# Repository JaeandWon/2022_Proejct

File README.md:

## 융합 프로젝트 10조
주제: PID 제어기를 이용한 밸런싱 로봇 제어

## 기술스택
- Control: PID, Complementary Filter 
- Protocol: mqtt, socket  
- Server: nodeJs  
- HW(MCU) : Arduino(esp32)
- PCB tool: KiCAD  

## Schematic 

## 3D Model

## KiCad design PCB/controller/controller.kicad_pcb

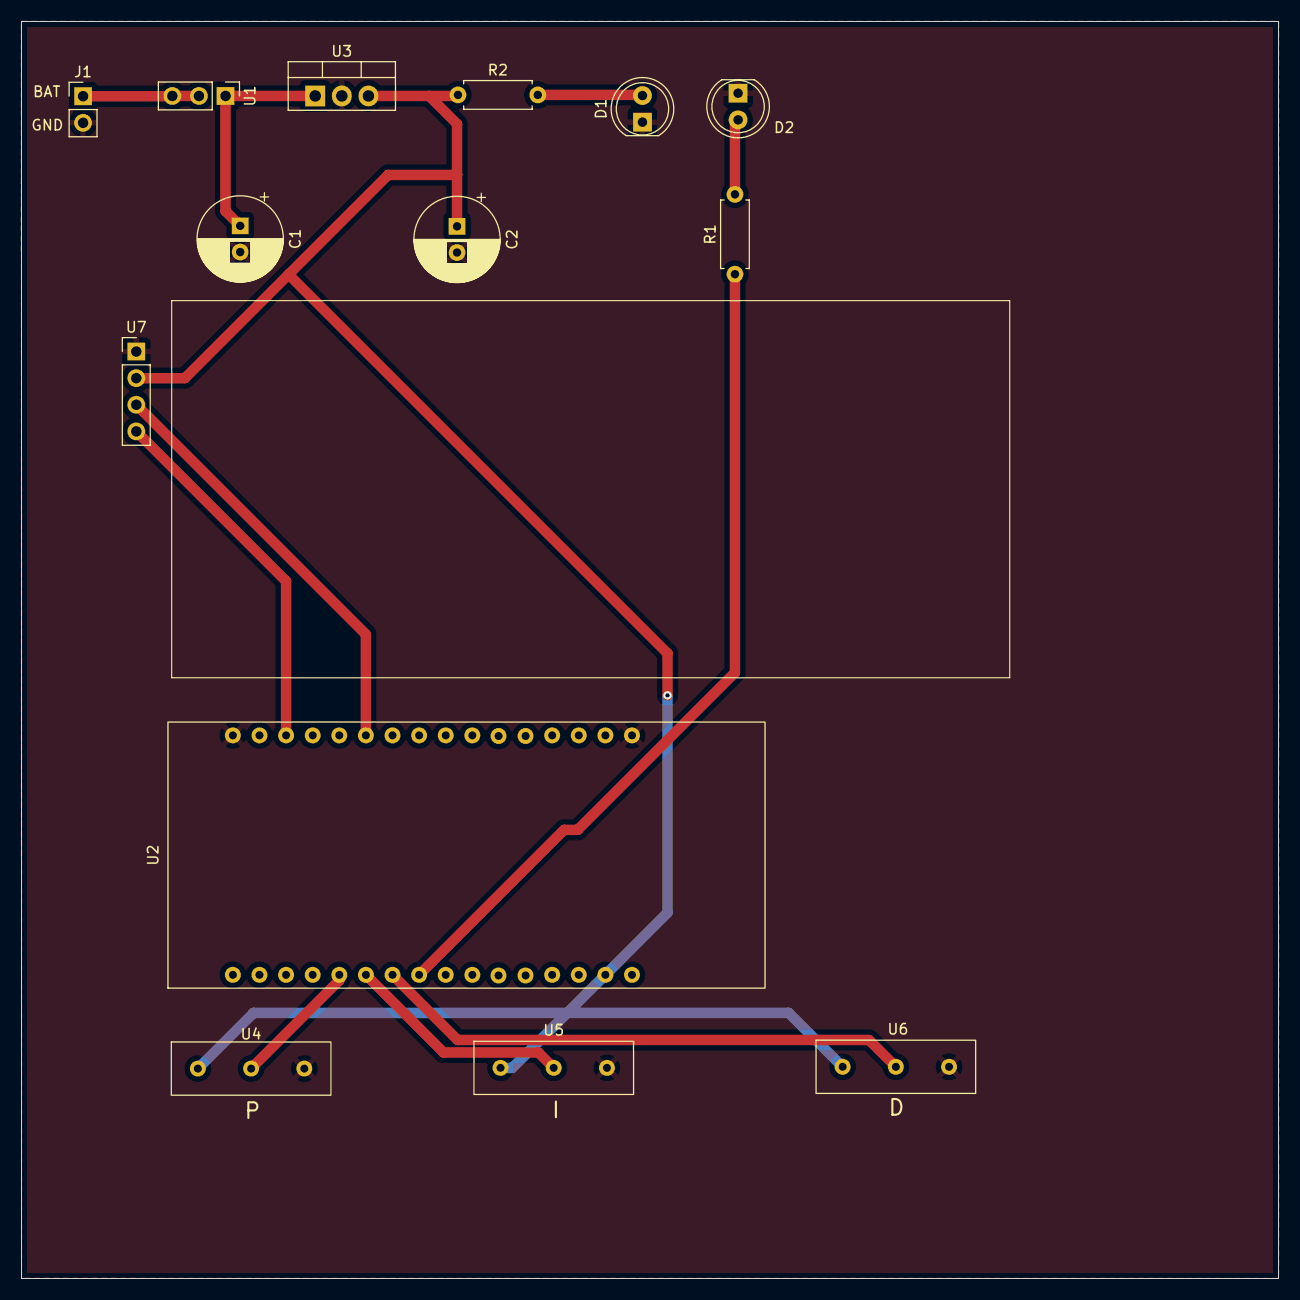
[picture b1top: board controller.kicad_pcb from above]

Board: 2 copper layers, 120.0 x 120.0 mm, 14 parts (0 on the bottom side), 12 nets.

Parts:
C1, C2: CAP; CP_Radial_D8.0mm_P2.50mm
D1, D2: LED; LED_D5.0mm
J1: Connector2; PinHeader_1x02_P2.54mm_Vertical
R1: 40; R_Axial_DIN0207_L6.3mm_D2.5mm_P7.62mm_Horizontal
R2: 330; R_Axial_DIN0207_L6.3mm_D2.5mm_P7.62mm_Horizontal
U1: Switch1; PinHeader_1x03_P2.54mm_Vertical
U2: Loline_d_32
U3: L7805; TO-220-3_Vertical
U4: Kp; variable_R
U5: Ki; variable_R
U6: Kd; variable_R
U7: LCD; PinHeader_1x04_P2.54mm_Vertical

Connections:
+5V: C2.1, R2.1, U2.USB, U3.3 (OUT), U4.1, U5.1, U6.1, U7.2
+BATT: C1.1, U1.1, U3.1 (IN)
+BATT_IN: J1.1, U1.2, U1.3
/Kd: U2.33, U6.2
/Ki: U2.32, U5.2
/Kp: U2.34, U4.2
/SCL: U2.22, U7.4
/SDA: U2.21, U7.3
/WF_LED2: R1.1, U2.25
GND: C1.2, C2.2, D1.1 (K), D2.1 (K), J1.2, U2.GND, U3.2 (GND), U4.3, U5.3, U6.3, U7.1
unnamed: D1.2 (A), R2.2
unnamed: D2.2 (A), R1.2

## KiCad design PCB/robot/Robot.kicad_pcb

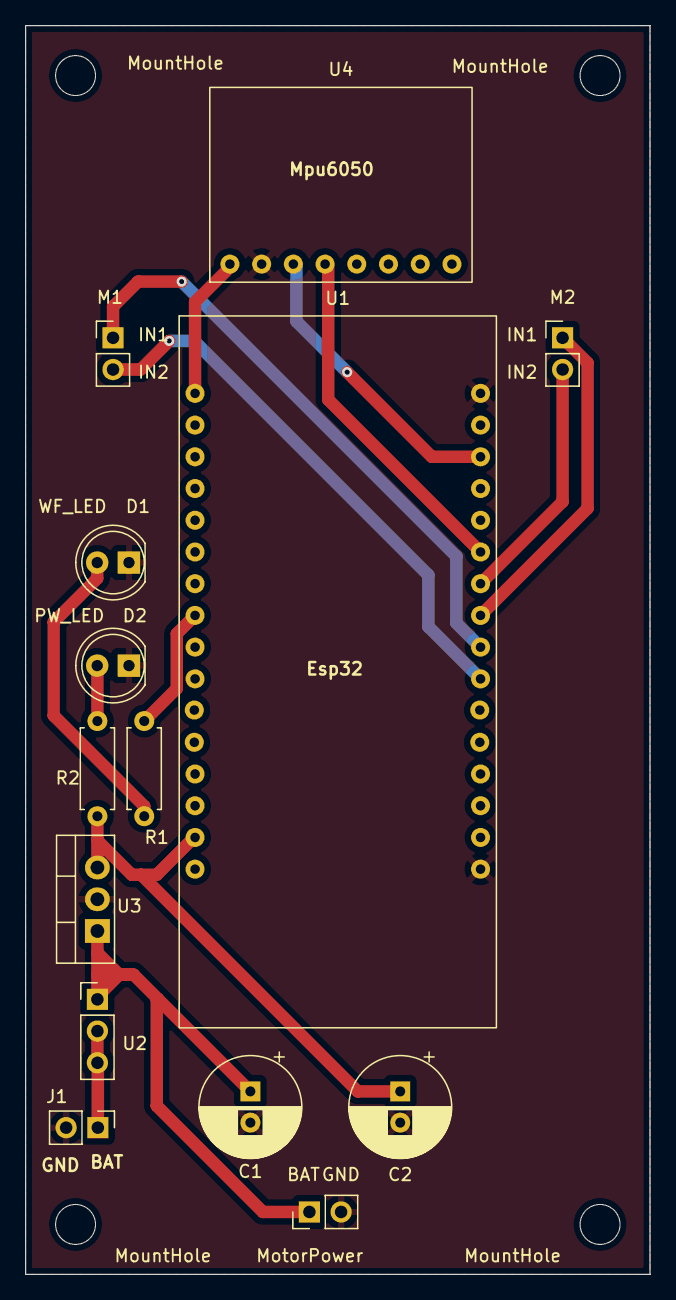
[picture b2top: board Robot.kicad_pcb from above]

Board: 2 copper layers, 50.0 x 100.0 mm, 18 parts (0 on the bottom side), 14 nets.

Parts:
C1: 0.33uF; CP_Radial_D8.0mm_P2.50mm
C2: 0.1uF; CP_Radial_D8.0mm_P2.50mm
D1, D2: LED; LED_D5.0mm
J1: PowerConnector; PinHeader_1x02_P2.54mm_Vertical
M1, M2: Motor_DC; PinHeader_1x02_P2.54mm_Vertical
MotorPower: Motor_DC; PinHeader_1x02_P2.54mm_Vertical
MountHole: MountingHole_3.2mm_M3
MountHole#2, MountHole#3, MountHole#4: MountingHole_3.2mm_M3
R1: 40; R_Axial_DIN0207_L6.3mm_D2.5mm_P7.62mm_Horizontal
R2: 330; R_Axial_DIN0207_L6.3mm_D2.5mm_P7.62mm_Horizontal
U1: Loline_d_32
U2: Switch1; PinHeader_1x03_P2.54mm_Vertical
U3: L7805; TO-220-3_Vertical
U4: Mpu6050

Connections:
+3V3: U1.3V, U4.VCC
+5V: C2.1, R2.1, U1.USB, U3.3 (OUT)
+BATT: C1.1, MotorPower.1 (+), U2.1, U3.1 (IN)
+BATT_IN: J1.1, U2.2, U2.3
/IN1: M1.1 (+), U1.5
/IN2: M1.2 (-), U1.17
/IN3: M2.1 (+), U1.18
/IN4: M2.2 (-), U1.19
/SCL: U1.22, U4.SCL
/SDA: U1.21, U4.SDA
/WF_LED: R1.1, U1.25
GND: C1.2, C2.2, D1.1 (K), D2.1 (K), J1.2, U1.GND, U3.2 (GND), U4.GND
unnamed: D1.2 (A), R1.2
unnamed: D2.2 (A), R2.2

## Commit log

2022-11-12 Update Server and Client
2022-11-14 Updarte Controller
2022-11-15 Update Self Balancing Robot
2022-11-15 Update README.md #2
2022-11-19 Update Schematics
2022-11-21 Update Gerber Files
